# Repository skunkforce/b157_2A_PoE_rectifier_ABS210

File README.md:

# edgy_board number b157
This design is part of the [edgy board project](https://github.com/skunkforce/edgy_boards). It provides a 2A PoE rectifier using ABS210.

# getting started
This repository uses submodules. After cloning use the command 

```$ git submodule update --init --recursive```

to pull the submodules before opening the project with kicad. 

# Tests
Tests can be found in [TESTS.md](TESTS.md)

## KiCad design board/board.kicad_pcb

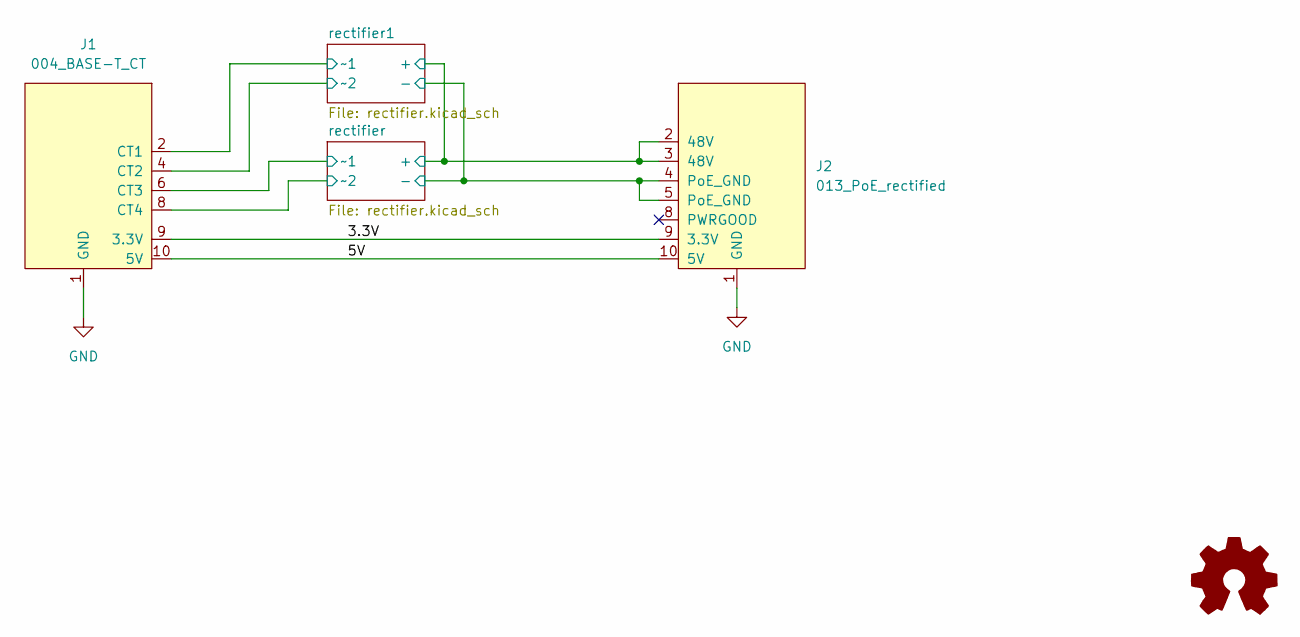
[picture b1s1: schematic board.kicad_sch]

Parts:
J1: 004_BASE-T_CT; on_edge_2x05_device
J2: 013_PoE_rectified; on_edge_2x05_host
LOGO1: Logo_Open_Hardware_Small; OSHW-Symbol_6.7x6mm_SilkScreen

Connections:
/3.3V: J1.9 (3.3V), J2.9 (3.3V)
/5V: J1.10 (5V), J2.10 (5V)
/rectifier1/~1: J1.2 (CT1); also elsewhere on the board
/rectifier1/~2: J1.4 (CT2); also elsewhere on the board
/rectifier/+: J2.2 (48V), J2.3 (48V); also elsewhere on the board
/rectifier/-: J2.4 (PoE_GND), J2.5 (PoE_GND); also elsewhere on the board
/rectifier/~1: J1.6 (CT3); also elsewhere on the board
/rectifier/~2: J1.8 (CT4); also elsewhere on the board
GND: J1.1 (GND), J2.1 (GND)

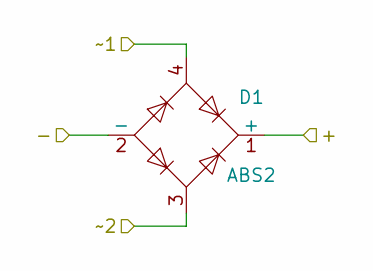
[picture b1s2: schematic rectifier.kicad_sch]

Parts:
D1: ABS2; Diode_Bridge_Diotec_ABS; LCSC C224221

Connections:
/rectifier/+: D1.1 (+); also elsewhere on the board
/rectifier/-: D1.2 (-); also elsewhere on the board
/rectifier/~1: D1.4; also elsewhere on the board
/rectifier/~2: D1.3; also elsewhere on the board

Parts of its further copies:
D2: ABS2; Diode_Bridge_Diotec_ABS; LCSC C224221

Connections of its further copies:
/rectifier1/~1: D2.4; also elsewhere on the board
/rectifier1/~2: D2.3; also elsewhere on the board
/rectifier/+: D2.1 (+); also elsewhere on the board
/rectifier/-: D2.2 (-); also elsewhere on the board

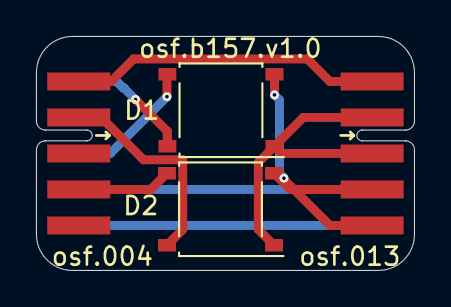
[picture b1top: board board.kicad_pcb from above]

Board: 2 copper layers, 21.0 x 13.0 mm, 5 parts (1 on the bottom side), 9 nets.

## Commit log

2024-02-16 initial
